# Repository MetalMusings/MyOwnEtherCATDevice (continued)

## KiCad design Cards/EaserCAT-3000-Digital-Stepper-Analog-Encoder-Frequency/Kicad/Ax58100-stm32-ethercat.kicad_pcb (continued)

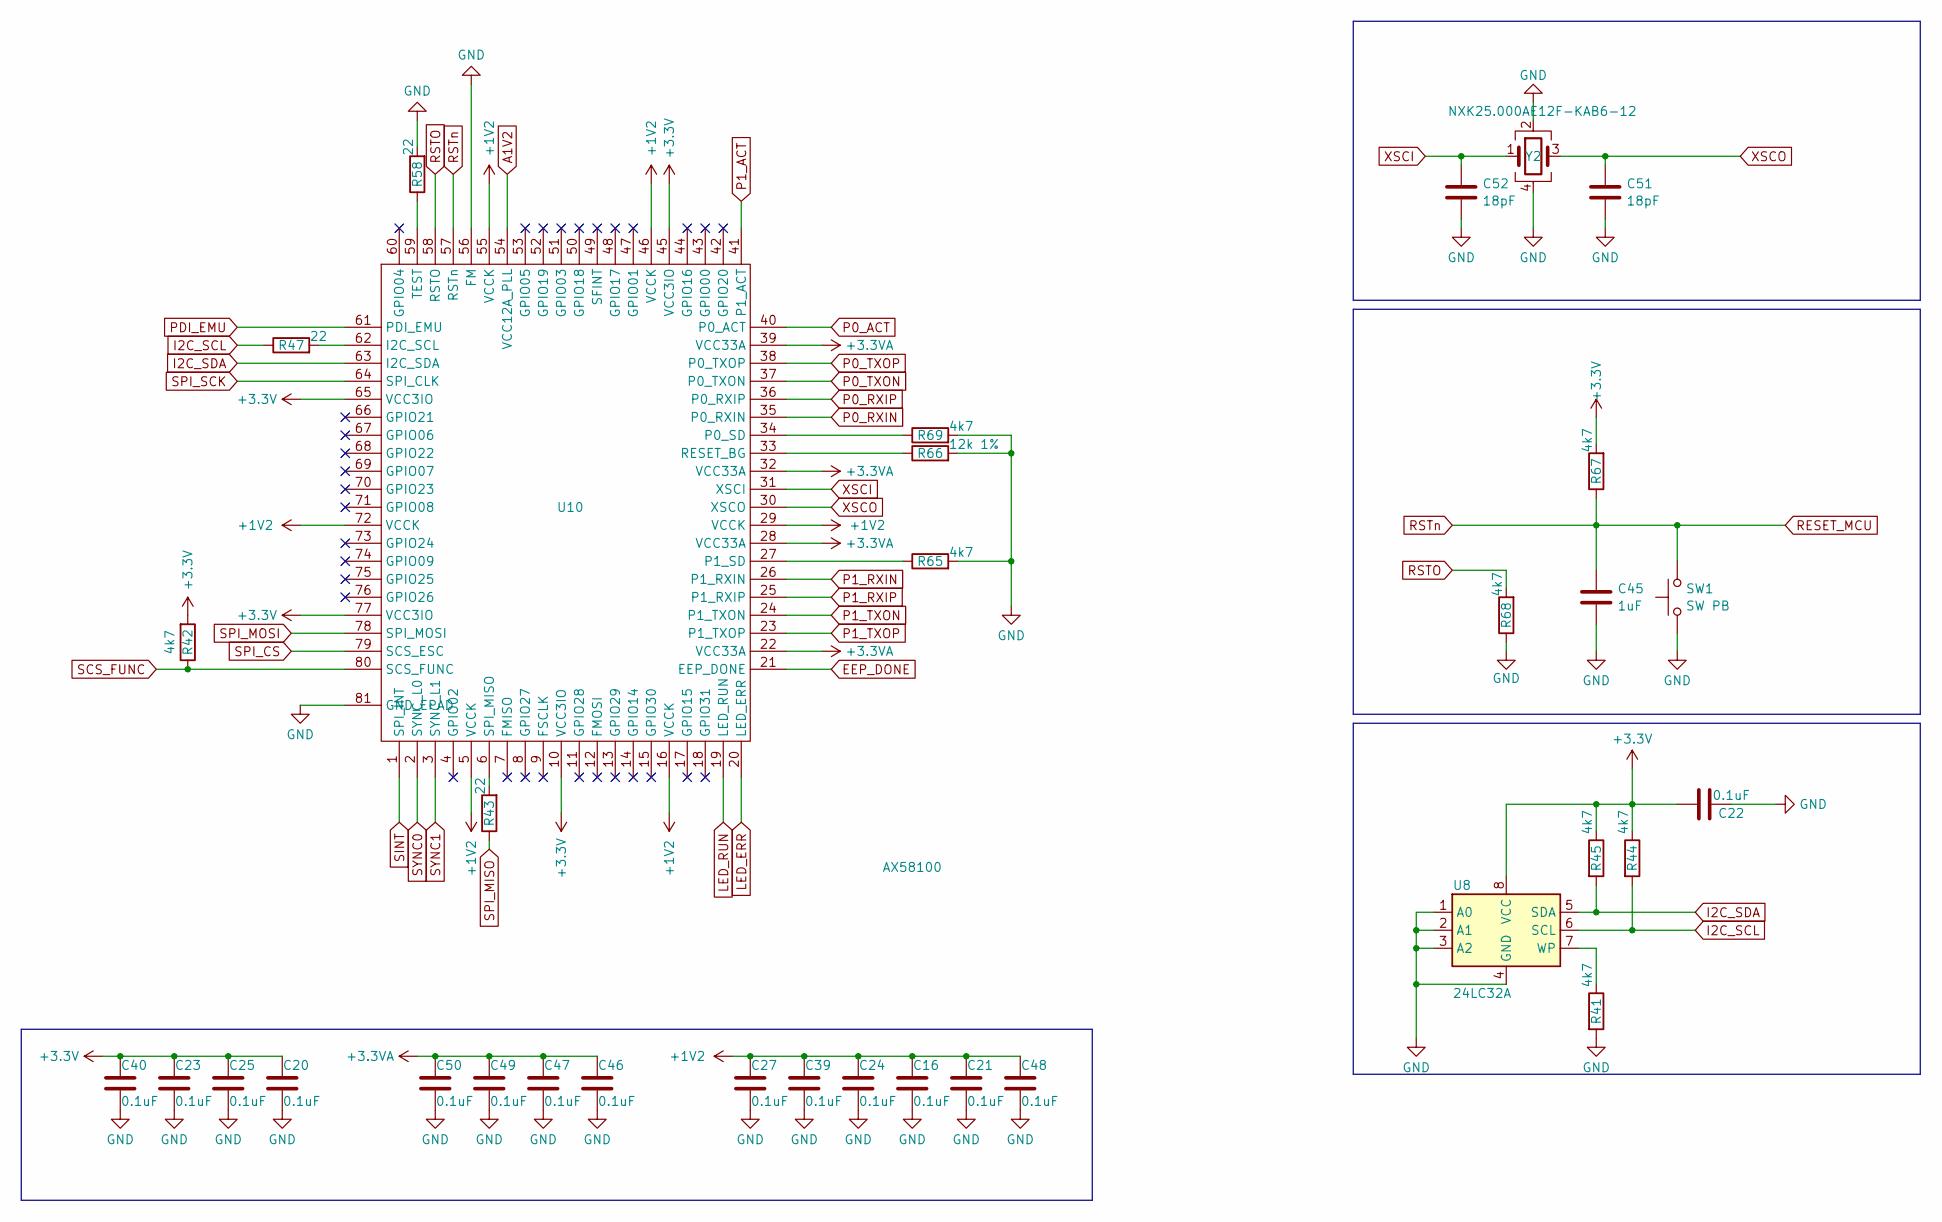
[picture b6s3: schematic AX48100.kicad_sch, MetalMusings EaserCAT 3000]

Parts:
C16, C20, C21, C22, C23, C24, C25, C27, C39, C40, C46, C47, C48, C49, C50: 0.1uF; C_0805_2012Metric
C45: 1uF; C_0805_2012Metric
C51, C52: 18pF; C_0805_2012Metric
R41, R44, R45, R65, R67, R68, R69: 4k7; R_0805_2012Metric
R42: 4k7; R_0603_1608Metric
R43, R47, R58: 22; R_0805_2012Metric
R66: 12k 1%; R_0805_2012Metric
SW1: SW PB; SW_Push_1P1T_XKB_TS-1187A
U8: 24LC32A; SOIC-8_3.9x4.9mm_P1.27mm
U10: AX58100; LQFP-80-1EP_10x10mm_P0.4mm_EP5.3x4.5mm_ThermalVias
Y2: NXK25.000AE12F-KAB6-12; Crystal_SMD_SeikoEpson_TSX3225-4Pin_3.2x2.5mm

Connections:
+1V2: C16.1, C21.1, C24.1, C27.1, C39.1, C48.1, U10.5 (VCCK), U10.16 (VCCK), U10.29 (VCCK), U10.46 (VCCK), U10.55 (VCCK), U10.72 (VCCK); also elsewhere on the board
+3.3V: C20.1, C22.2, C23.1, C25.1, C40.1, R42.2, R44.1, R45.1, R67.2, U8.8 (VCC), U10.10 (VCC3IO), U10.45 (VCC3IO), U10.65 (VCC3IO), U10.77 (VCC3IO); also elsewhere on the board
+3.3VA: C46.1, C47.1, C49.1, C50.1, U10.22 (VCC33A), U10.28 (VCC33A), U10.32 (VCC33A), U10.39 (VCC33A); also elsewhere on the board
A1V2: U10.54 (VCC12A_PLL); also elsewhere on the board
EEP_DONE: U10.21 (EEP_DONE); also elsewhere on the board
GND: C16.2, C20.2, C21.2, C22.1, C23.2, C24.2, C25.2, C27.2, C39.2, C40.2, C45.2, C46.2, C47.2, C48.2, C49.2, C50.2, C51.2, C52.2, R41.2, R58.2, R65.2, R66.2, R68.1, R69.2, SW1.1, U8.1 (A0), U8.2 (A1), U8.3 (A2), U8.4 (GND), U10.56 (FM), U10.81 (GND_EPAD), Y2.2, Y2.4; also elsewhere on the board
I2C_SCL: R44.2, R47.1, U8.6 (SCL)
I2C_SDA: R45.2, U8.5 (SDA), U10.63 (I2C_SDA)
LED_ERR: U10.20 (LED_ERR); also elsewhere on the board
LED_RUN: U10.19 (LED_RUN); also elsewhere on the board
unnamed: R41.1, U8.7 (WP)
unnamed: R47.2, U10.62 (I2C_SCL)
unnamed: R69.1, U10.34 (P0_SD)
unnamed: R65.1, U10.27 (P1_SD)
unnamed: R66.1, U10.33 (RESET_BG)
unnamed: R43.2, U10.6 (SPI_MISO)
unnamed: R58.1, U10.59 (TEST)
P0_ACT: U10.40 (P0_ACT); also elsewhere on the board
P0_RXIN: U10.35 (P0_RXIN); also elsewhere on the board
P0_RXIP: U10.36 (P0_RXIP); also elsewhere on the board
P0_TXON: U10.37 (P0_TXON); also elsewhere on the board
P0_TXOP: U10.38 (P0_TXOP); also elsewhere on the board
P1_ACT: U10.41 (P1_ACT); also elsewhere on the board
P1_RXIN: U10.26 (P1_RXIN); also elsewhere on the board
P1_RXIP: U10.25 (P1_RXIP); also elsewhere on the board
P1_TXON: U10.24 (P1_TXON); also elsewhere on the board
P1_TXOP: U10.23 (P1_TXOP); also elsewhere on the board
PDI_EMU: U10.61 (PDI_EMU); also elsewhere on the board
RESET_MCU: C45.1, R67.1, SW1.2, U10.57 (RSTn); also elsewhere on the board
RSTO: R68.2, U10.58 (RSTO)
SCS_FUNC: R42.1, U10.80 (SCS_FUNC); also elsewhere on the board
SINT: U10.1 (SPI_INT); also elsewhere on the board
SPI_CS: U10.79 (SCS_ESC); also elsewhere on the board
SPI_MISO: R43.1; also elsewhere on the board
SPI_MOSI: U10.78 (SPI_MOSI); also elsewhere on the board
SPI_SCK: U10.64 (SPI_CLK); also elsewhere on the board
SYNC0: U10.2 (SYNC_L0); also elsewhere on the board
SYNC1: U10.3 (SYNC_L1); also elsewhere on the board
XSCI: C52.1, U10.31 (XSCI), Y2.1
XSCO: C51.1, U10.30 (XSCO), Y2.3

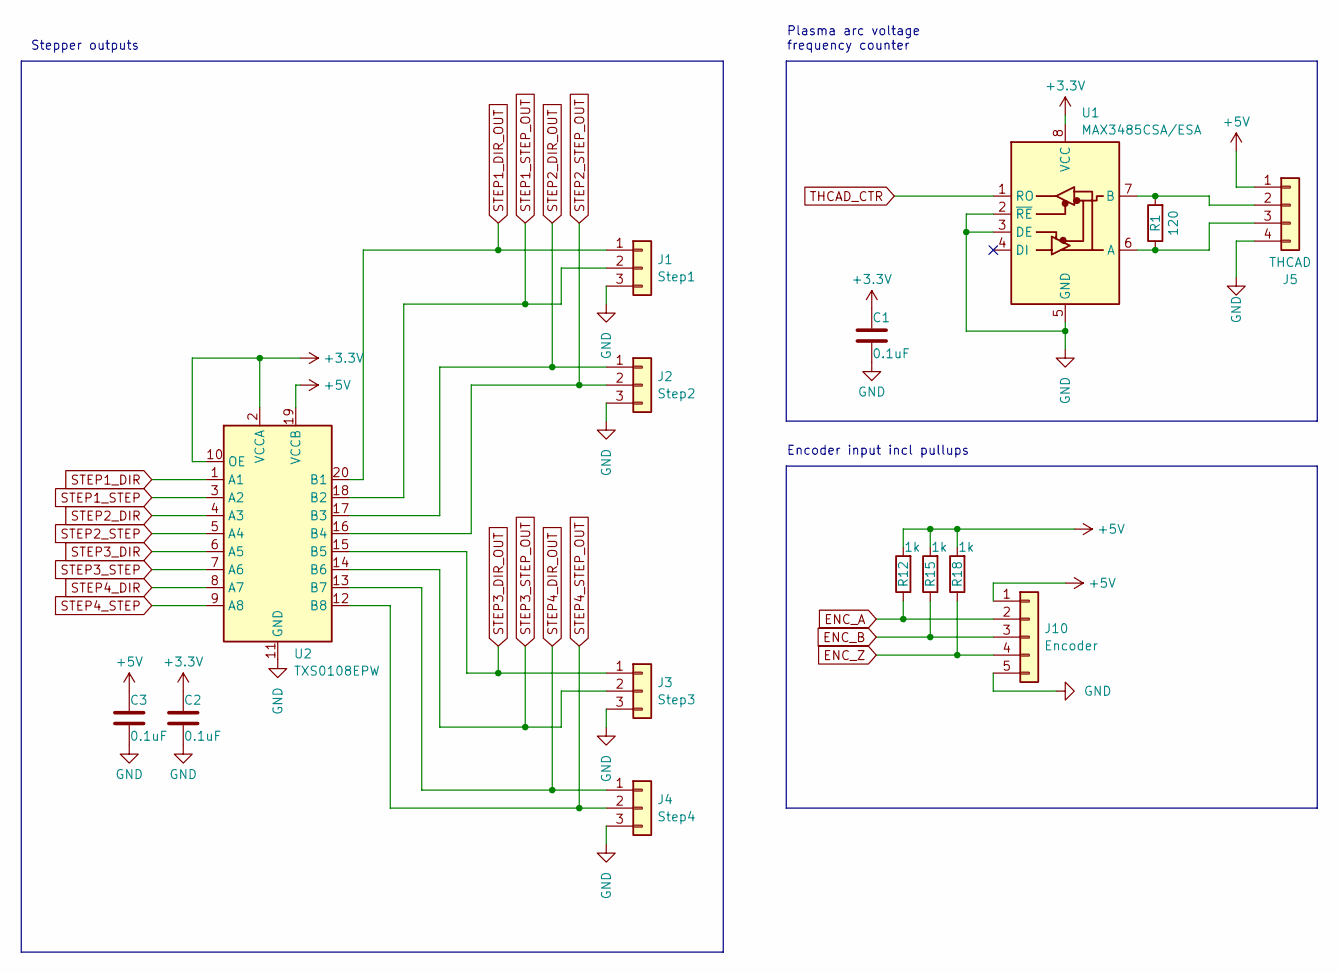
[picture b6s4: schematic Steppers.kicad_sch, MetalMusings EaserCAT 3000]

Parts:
C1, C2, C3: 0.1uF; C_0805_2012Metric
J1: Step1; PhoenixContact_MCV_1,5_3-G-3.5_1x03_P3.50mm_Vertical
J2: Step2; PhoenixContact_MCV_1,5_3-G-3.5_1x03_P3.50mm_Vertical
J3: Step3; PhoenixContact_MCV_1,5_3-G-3.5_1x03_P3.50mm_Vertical
J4: Step4; PhoenixContact_MCV_1,5_3-G-3.5_1x03_P3.50mm_Vertical
J5: THCAD; PhoenixContact_MCV_1,5_4-G-3.5_1x04_P3.50mm_Vertical
J10: Encoder; PhoenixContact_MCV_1,5_5-G-3.5_1x05_P3.50mm_Vertical
R1: 120; R_0805_2012Metric
R12, R15, R18: 1k; R_0805_2012Metric
U1: MAX3485CSA/ESA; SO-8_3.9x4.9mm_P1.27mm
U2: TXS0108EPW; TSSOP-20_4.4x6.5mm_P0.65mm

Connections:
+3.3V: C1.1, C2.1, U1.8 (VCC), U2.2 (VCCA), U2.10 (OE); also elsewhere on the board
+5V: C3.1, J5.1, J10.1, R12.2, R15.2, R18.2, U2.19 (VCCB); also elsewhere on the board
ENC_A: J10.2, R12.1; also elsewhere on the board
ENC_B: J10.3, R15.1; also elsewhere on the board
ENC_Z: J10.4, R18.1; also elsewhere on the board
GND: C1.2, C2.2, C3.2, J1.3, J2.3, J3.3, J4.3, J5.4, J10.5, U1.2 (~RE), U1.3 (DE), U1.5 (GND), U2.11 (GND); also elsewhere on the board
unnamed: J5.2, R1.2, U1.7 (B)
unnamed: J5.3, R1.1, U1.6 (A)
STEP1_DIR: U2.1 (A1); also elsewhere on the board
STEP1_DIR_OUT: J1.1, U2.20 (B1)
STEP1_STEP: U2.3 (A2); also elsewhere on the board
STEP1_STEP_OUT: J1.2, U2.18 (B2)
STEP2_DIR: U2.4 (A3); also elsewhere on the board
STEP2_DIR_OUT: J2.1, U2.17 (B3)
STEP2_STEP: U2.5 (A4); also elsewhere on the board
STEP2_STEP_OUT: J2.2, U2.16 (B4)
STEP3_DIR: U2.6 (A5); also elsewhere on the board
STEP3_DIR_OUT: J3.1, U2.15 (B5)
STEP3_STEP: U2.7 (A6); also elsewhere on the board
STEP3_STEP_OUT: J3.2, U2.14 (B6)
STEP4_DIR: U2.8 (A7); also elsewhere on the board
STEP4_DIR_OUT: J4.1, U2.13 (B7)
STEP4_STEP: U2.9 (A8); also elsewhere on the board
STEP4_STEP_OUT: J4.2, U2.12 (B8)
THCAD_CTR: U1.1 (RO); also elsewhere on the board

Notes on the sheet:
Encoder input incl pullups
Plasma arc voltage frequency counter
Stepper outputs

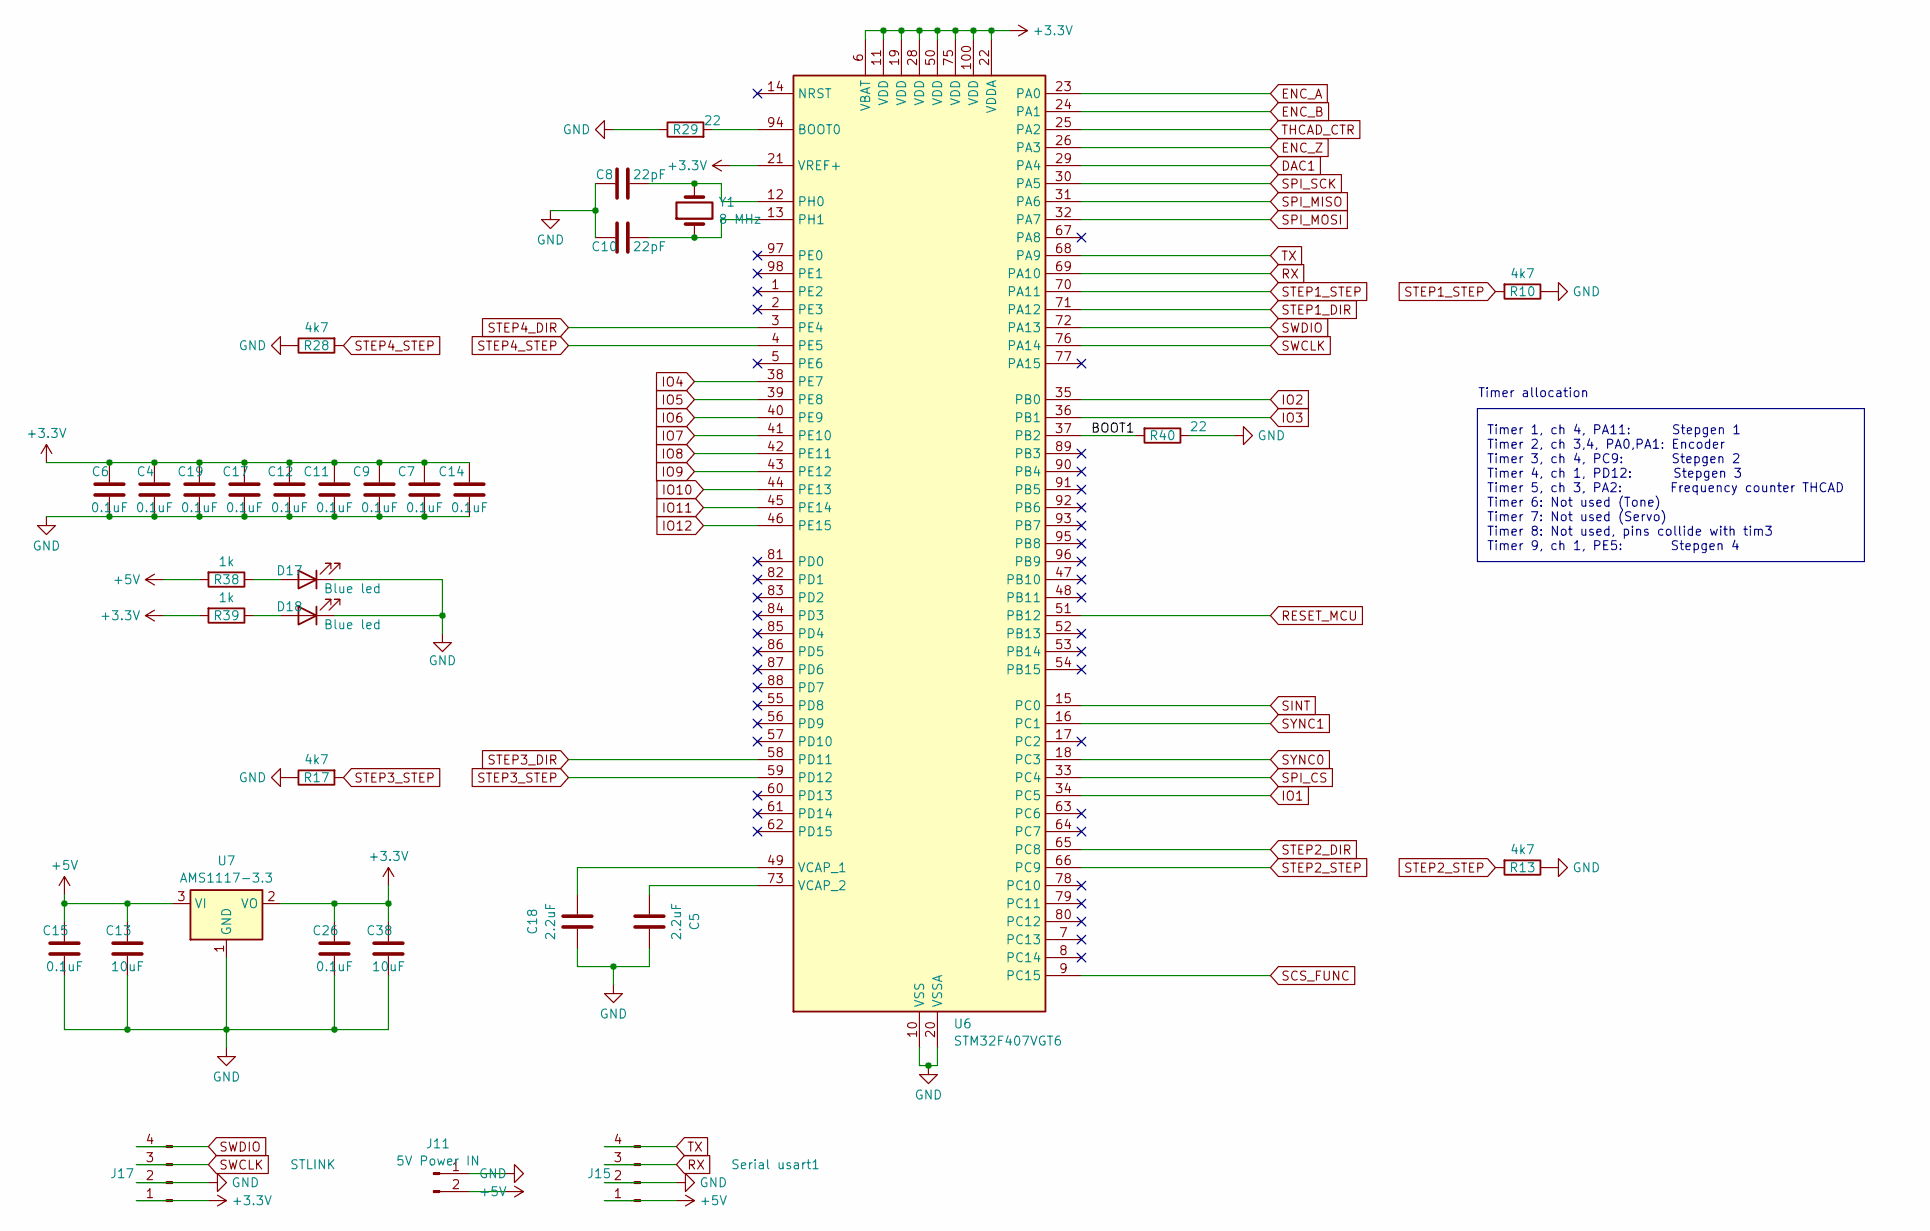
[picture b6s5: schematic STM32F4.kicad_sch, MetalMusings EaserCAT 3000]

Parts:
C4, C6, C7, C9, C11, C12, C14, C15, C17, C19, C26: 0.1uF; C_0805_2012Metric
C5, C18: 2.2uF; C_0805_2012Metric
C8, C10: 22pF; C_0805_2012Metric
C13, C38: 10uF; C_0805_2012Metric
D17, D18: Blue led; LED_0603_1608Metric
J11: 5V Power IN; PhoenixContact_MCV_1,5_2-G-3.5_1x02_P3.50mm_Vertical
J15: Serial usart1; JST_XH_B4B-XH-A_1x04_P2.50mm_Vertical
J17: STLINK; JST_XH_B4B-XH-A_1x04_P2.50mm_Vertical
R10, R13, R17, R28: 4k7; R_0805_2012Metric
R29, R40: 22; R_0805_2012Metric
R38, R39: 1k; R_0805_2012Metric
U6: STM32F407VGT6; LQFP-100_14x14mm_P0.5mm
U7: AMS1117-3.3; SOT-223-3_TabPin2
Y1: 8 MHz; Crystal_HC49-4H_Vertical

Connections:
+3.3V: C4.1, C6.1, C7.1, C9.1, C11.1, C12.1, C14.1, C17.1, C19.1, C26.1, C38.1, J17.1, R39.2, U6.6 (VBAT), U6.11 (VDD), U6.19 (VDD), U6.21 (VREF+), U6.22 (VDDA), U6.28 (VDD), U6.50 (VDD), U6.75 (VDD), U6.100 (VDD), U7.2 (VO); also elsewhere on the board
+5V: C13.1, C15.1, J11.2, J15.1, R38.2, U7.3 (VI); also elsewhere on the board
/STM32F4/BOOT1: R40.2, U6.37 (PB2)
DAC1: U6.29 (PA4); also elsewhere on the board
ENC_A: U6.23 (PA0); also elsewhere on the board
ENC_B: U6.24 (PA1); also elsewhere on the board
ENC_Z: U6.26 (PA3); also elsewhere on the board
GND: C4.2, C5.1, C6.2, C7.2, C8.1, C9.2, C10.1, C11.2, C12.2, C13.2, C14.2, C15.2, C17.2, C18.1, C19.2, C26.2, C38.2, D17.1 (K), D18.1 (K), J11.1, J15.2, J17.2, R10.1, R13.1, R17.1, R28.1, R29.1, R40.1, U6.10 (VSS), U6.20 (VSSA), U6.27 (VSS), U6.74 (VSS), U6.99 (VSS), U7.1 (GND); also elsewhere on the board
IO1: U6.34 (PC5); also elsewhere on the board
IO2: U6.35 (PB0); also elsewhere on the board
IO3: U6.36 (PB1); also elsewhere on the board
IO4: U6.38 (PE7); also elsewhere on the board
IO5: U6.39 (PE8); also elsewhere on the board
IO6: U6.40 (PE9); also elsewhere on the board
IO7: U6.41 (PE10); also elsewhere on the board
IO8: U6.42 (PE11); also elsewhere on the board
IO9: U6.43 (PE12); also elsewhere on the board
IO10: U6.44 (PE13); also elsewhere on the board
IO11: U6.45 (PE14); also elsewhere on the board
IO12: U6.46 (PE15); also elsewhere on the board
unnamed: D17.2 (A), R38.1
unnamed: D18.2 (A), R39.1
unnamed: R29.2, U6.94 (BOOT0)
unnamed: C8.2, U6.12 (PH0), Y1.2
unnamed: C10.2, U6.13 (PH1), Y1.1
unnamed: C18.2, U6.49 (VCAP_1)
unnamed: C5.2, U6.73 (VCAP_2)
RESET_MCU: U6.51 (PB12); also elsewhere on the board
RX: J15.3, U6.69 (PA10)
SCS_FUNC: U6.9 (PC15); also elsewhere on the board
SINT: U6.15 (PC0); also elsewhere on the board
SPI_CS: U6.33 (PC4); also elsewhere on the board
SPI_MISO: U6.31 (PA6); also elsewhere on the board
SPI_MOSI: U6.32 (PA7); also elsewhere on the board
SPI_SCK: U6.30 (PA5); also elsewhere on the board
STEP1_DIR: U6.71 (PA12); also elsewhere on the board
STEP1_STEP: R10.2, U6.70 (PA11); also elsewhere on the board
STEP2_DIR: U6.65 (PC8); also elsewhere on the board
STEP2_STEP: R13.2, U6.66 (PC9); also elsewhere on the board
STEP3_DIR: U6.58 (PD11); also elsewhere on the board
STEP3_STEP: R17.2, U6.59 (PD12); also elsewhere on the board
STEP4_DIR: U6.3 (PE4); also elsewhere on the board
STEP4_STEP: R28.2, U6.4 (PE5); also elsewhere on the board
SWCLK: J17.3, U6.76 (PA14)
SWDIO: J17.4, U6.72 (PA13)
SYNC0: U6.18 (PC3); also elsewhere on the board
SYNC1: U6.16 (PC1); also elsewhere on the board
THCAD_CTR: U6.25 (PA2); also elsewhere on the board
TX: J15.4, U6.68 (PA9)

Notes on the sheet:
Timer allocation
Timer 1, ch 4, PA11: Stepgen 1 Timer 2, ch 3,4, PA0,PA1: Encoder Timer 3, ch 4, PC9: Stepgen 2 Timer 4, ch 1, PD12: Stepgen 3 Timer 5, ch 3, PA2: Frequency counter THCAD Timer 6: Not used (Tone) Timer 7: Not used (Servo) Timer 8: Not used, pins collide with tim3 Timer 9, ch 1, PE5: Stepgen 4

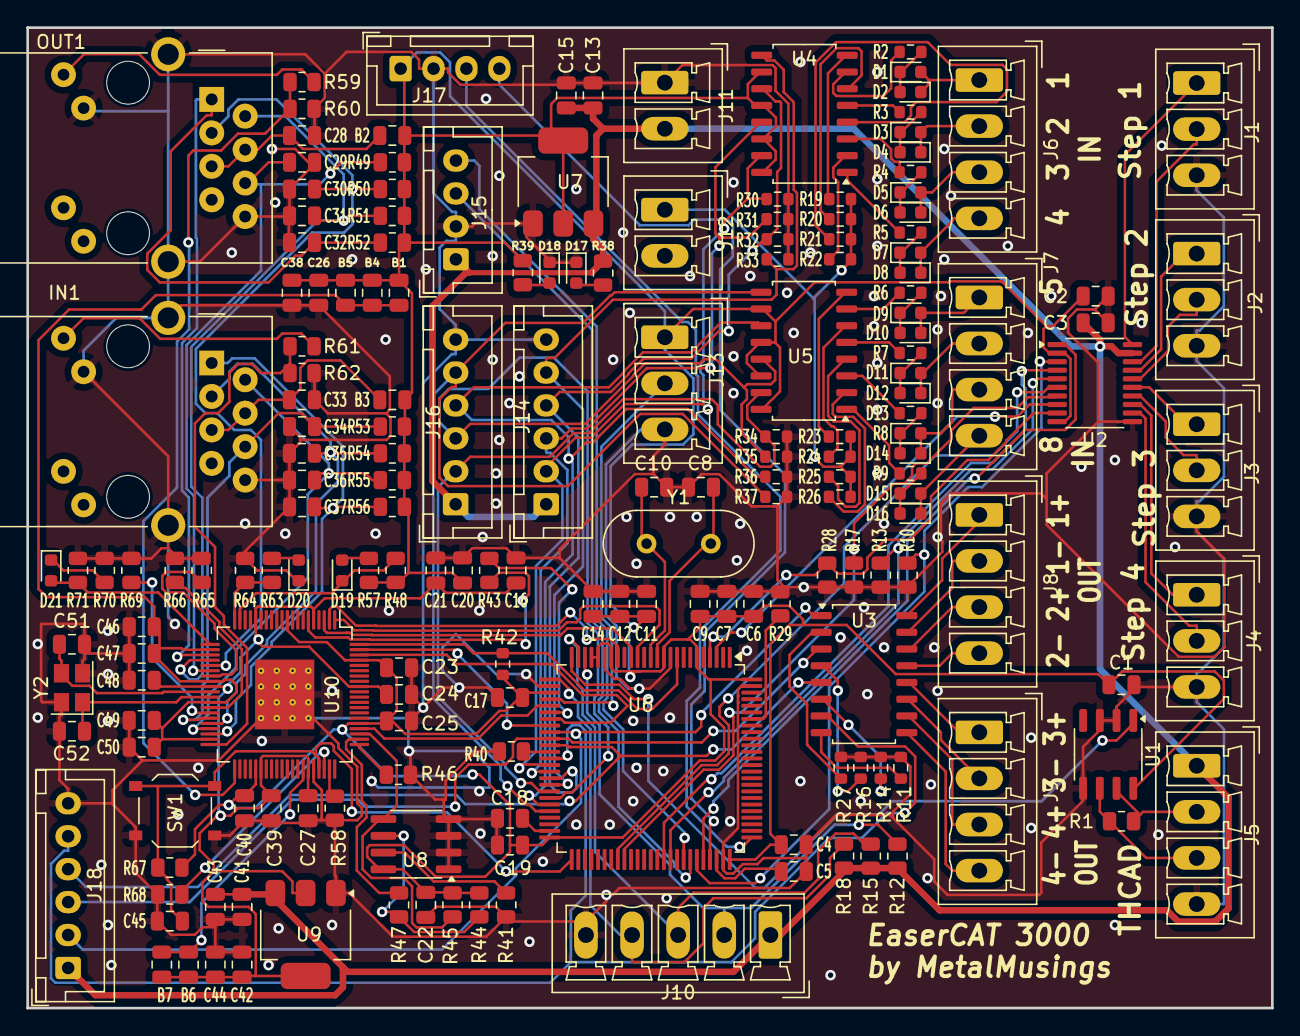
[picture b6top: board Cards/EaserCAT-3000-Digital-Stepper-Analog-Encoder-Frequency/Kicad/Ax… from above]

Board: 2 copper layers, 94.5 x 74.4 mm, 184 parts (0 on the bottom side), 140 nets.

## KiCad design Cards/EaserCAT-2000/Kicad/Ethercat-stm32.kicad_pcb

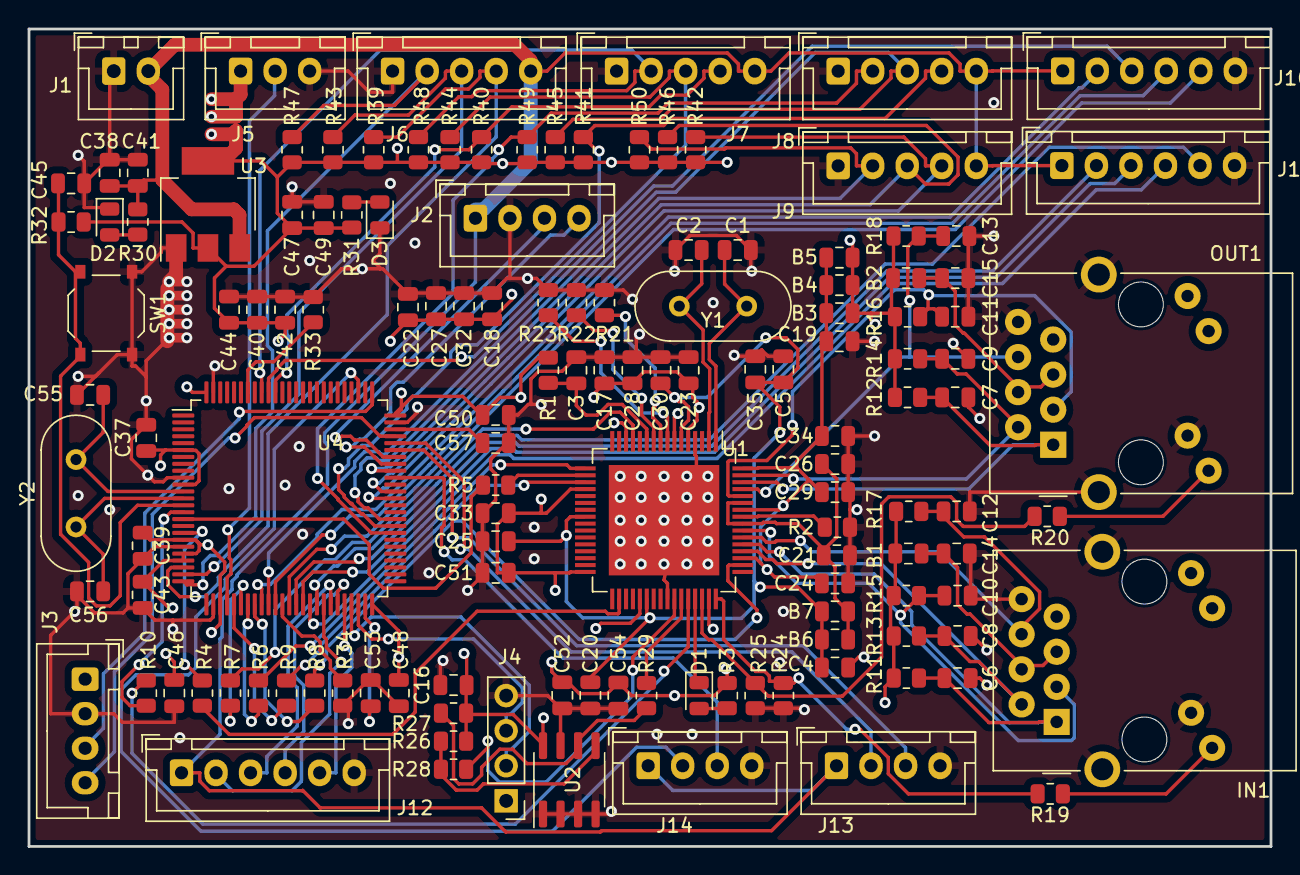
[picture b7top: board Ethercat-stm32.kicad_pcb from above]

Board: 4 copper layers, 89.9 x 59.2 mm, 134 parts (0 on the bottom side), 91 nets.

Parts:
B1, B2: BLM18EG221S; C_0805_2012Metric
B3, B4, B5, B6, B7: BLM18EG221SN1D; C_0805_2012Metric
C1, C2: 20pF; C_0805_2012Metric
C3, C14, C15, C16, C17, C18, C19, C20, C21, C22, C23, C24, C25, C26, C27, C28, C29, C30, C32, C33, C34, C35, C37, C38, C39, C40, C42, C43, C44, C45, C46, C47, C48, C50, C51, C52, C54: 0.1uF; C_0805_2012Metric
C4: 470pF; C_0805_2012Metric
C5: 1uF; C_0805_2012Metric
C6, C7, C8, C9, C10, C11, C12, C13: 10pF; C_0805_2012Metric
C41, C49: 10uF; C_0805_2012Metric
C53, C57: 2.2uF; C_0805_2012Metric
C55, C56: 22pF; C_0805_2012Metric
D1: Green led; LED_0805_2012Metric
D2, D3: Blue led; LED_0805_2012Metric
IN1: J0011D01BNL; PulseJack JB0011D01BNL
J1: Conn_01x02_Pin; JST_XH_B2B-XH-A_1x02_P2.50mm_Vertical
J2: Serial usart1; JST_XH_B4B-XH-A_1x04_P2.50mm_Vertical
J3: STLINK; JST_XH_B4B-XH-A_1x04_P2.50mm_Vertical
J4: I2C bus2; PinHeader_1x04_P2.54mm_Vertical
J5: DAC1; JST_XH_B3B-XH-A_1x03_P2.50mm_Vertical
J6: Encoder 1; JST_XH_B5B-XH-A_1x05_P2.50mm_Vertical
J7: Encoder 2; JST_XH_B5B-XH-A_1x05_P2.50mm_Vertical
J8: Encoder 3; JST_XH_B5B-XH-A_1x05_P2.50mm_Vertical
J9: Encoder 4; JST_XH_B5B-XH-A_1x05_P2.50mm_Vertical
J10, J11, J12: Conn_01x06_Pin; JST_XH_B6B-XH-A_1x06_P2.50mm_Vertical
J13: Stepper 1; JST_XH_B4B-XH-A_1x04_P2.50mm_Vertical
J14: Stepper 2; JST_XH_B4B-XH-A_1x04_P2.50mm_Vertical
OUT1: J0011D01BNL; PulseJack JB0011D01BNL
R1, R21, R22, R23, R24, R25: 10k; R_0805_2012Metric
R2: 12.1k; R_0805_2012Metric
R3, R19, R20, R30, R31, R32, R39, R40, R41, R42, R43, R44, R45, R46, R47, R48, R49, R50: 1k; R_0805_2012Metric
R4, R5, R6, R7, R8, R9, R10, R28, R29, R33, R34: 22; R_0805_2012Metric
R11, R12, R13, R14, R15, R16, R17, R18: 49.9; R_0805_2012Metric
R26, R27: 2k; R_0805_2012Metric
SW1: SW_Push; SW_Push_1P1T_XKB_TS-1187A
U1: LAN9252_PT; TQFP-64-1EP_10x10mm_P0.5mm_EP8x8mm
U2: AT24CS32-SSHM; SOIC-8_3.9x4.9mm_P1.27mm
U3: AMS1117-3.3; SOT-223-3_TabPin2
U4: STM32F407VGT6; LQFP-100_14x14mm_P0.5mm
Y1: 25MHz; Crystal_HC49-U_Vertical
Y2: 8 MHz; Crystal_HC49-U_Vertical

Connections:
+1V2: B6.1, B7.1, C4.1, C5.1, C20.1, C25.1, C30.1, C35.1, U1.6 (VDDCR), U1.24 (VDDCR), U1.38 (VDDCR)
+3.3V: B1.1, B2.1, B3.1, B4.1, B5.1, C16.2, C17.1, C18.1, C22.1, C23.1, C27.1, C28.1, C32.1, C33.1, C37.1, C39.1, C40.1, C42.1, C43.1, C44.1, C46.1, C47.1, C48.1, C49.1, C50.1, C51.1, C52.1, C54.1, J3.1, J4.1, J5.1, R1.1, R3.1, R11.2, R12.2, R13.2, R14.2, R15.2, R16.2, R17.2, R18.2, R26.1, R27.1, R31.2, R32.2, R39.2, R40.2, R41.2, R42.2, R43.2, R44.2, R45.2, R46.2, R47.2, R48.2, R49.2, R50.2, U1.5 (VDD33), U1.7 (REG_EN), U1.14 (VDDIO), U1.20 (VDDIO), U1.32 (VDDIO), U1.37 (VDDIO), U1.47 (VDDIO), U2.8 (VCC), U3.2 (VO), U4.6 (VBAT), U4.11 (VDD), U4.19 (VDD), U4.21 (VREF+), U4.22 (VDDA), U4.28 (VDD), U4.50 (VDD), U4.75 (VDD), U4.100 (VDD)
+3.3VA: B3.2, B4.2, B5.2, C19.1, C24.1, C29.1, C34.1, U1.51 (VDD33TXRX1), U1.58 (VDD33BIAS), U1.64 (VDD33TXRX2)
+5V: C38.1, C41.1, J1.2, J2.1, J6.5, J7.5, J8.5, J9.5, J10.1, J11.1, J12.1, J13.1, J14.1, R30.2, U3.3 (VI)
/STM32F4/BOOT1: R34.2, U4.37 (PB2)
DAC1: J5.2, U4.29 (PA4)
ENC1_A: J6.4, R39.1, U4.23 (PA0)
ENC1_B: J6.3, R43.1, U4.24 (PA1)
ENC1_Z: J6.2, R47.1, U4.25 (PA2)
ENC2_A: J7.4, R40.1, U4.90 (PB4)
ENC2_B: J7.3, R44.1, U4.91 (PB5)
ENC2_Z: J7.2, R48.1, U4.92 (PB6)
ENC3_A: J8.4, R41.1, U4.59 (PD12)
ENC3_B: J8.3, R45.1, U4.60 (PD13)
ENC3_Z: J8.2, R49.1, U4.58 (PD11)
ENC4_A: J9.4, R42.1, U4.63 (PC6)
ENC4_B: J9.3, R46.1, U4.64 (PC7)
ENC4_Z: J9.2, R50.1, U4.67 (PA8)
FXLOSA: R21.1, U1.9 (FXSDA/FXLOSA/~FXSDENA)
FXLOSB: R22.1, U1.10 (FXSDB/FXLOSB/~FXSDENB)
FXLOSEN: R23.1, U1.8 (~FXLOSEN)
GND: C1.1, C2.1, C3.1, C4.2, C5.2, C6.1, C7.1, C8.1, C9.1, C10.1, C11.1, C12.1, C13.1, C14.1, C15.1, C16.1, C17.2, C18.2, C19.2, C20.2, C21.2, C22.2, C23.2, C24.2, C25.2, C26.2, C27.2, C28.2, C29.2, C30.2, C32.2, C33.2, C34.2, C35.2, C37.2, C38.2, C39.2, C40.2, C41.2, C42.2, C43.2, C44.2, C45.1, C46.2, C47.2, C48.2, C49.2, C50.2, C51.2, C52.2, C53.1, C54.2, C55.1, C56.1, C57.1, D2.1 (K), D3.1 (K), IN1.8 (CHS_GND), IN1.10, IN1.SH (CHS_GND), J1.1, J2.2, J3.2, J4.4, J5.3, J6.1, J7.1, J8.1, J9.1, J10.6, J11.6, J12.6, J13.4, J14.4, OUT1.8 (CHS_GND), OUT1.10, OUT1.SH (CHS_GND), R2.1, R21.2, R22.2, R23.2, R24.2, R25.2, R33.1, R34.1, SW1.1, U1.4 (OSCVSS), U1.41 (TESTMODE), U1.65 (VSS), U2.1 (A0), U2.2 (A1), U2.3 (A2), U2.4 (GND), U2.7 (WP), U3.1 (GND), U4.10 (VSS), U4.20 (VSSA), U4.27 (VSS), U4.74 (VSS), U4.99 (VSS)
GPIO0: R19.1, R24.1, U1.48 (LINKACTLED0/TDO/~CHIP_MODE0)
GPIO1: R20.1, R25.1, U1.46 (LINKACTLED1/TDI/~CHIP_MODE1)
I2C2_SCL: J4.2, U4.47 (PB10)
I2C2_SDA: J4.3, U4.48 (PB11)
I2C_SCL: R29.1, U1.43 (EESCL/TCK)
I2C_SDA: R28.1, U1.42 (EESDA/TMS)
IO1: J10.2, U4.34 (PC5)
IO2: J10.3, U4.35 (PB0)
IO3: J10.4, U4.36 (PB1)
IO4: J10.5, U4.38 (PE7)
IO5: J11.2, U4.39 (PE8)
IO6: J11.3, U4.40 (PE9)
IO7: J11.4, U4.41 (PE10)
IO8: J11.5, U4.42 (PE11)
IO9: J12.2, U4.43 (PE12)
IO10: J12.3, U4.44 (PE13)
IO11: J12.4, U4.45 (PE14)
IO12: J12.5, U4.46 (PE15)
IRQ: R10.1, U4.15 (PC0)
NRST: C45.2, R32.1, SW1.2, U4.14 (NRST)
unnamed: D1.2 (A), R3.2
unnamed: D1.1 (K), U1.45 (RUNLED/~E2PSIZE)
unnamed: D2.2 (A), R30.1
unnamed: D3.2 (A), R31.1
unnamed: IN1.9, R19.2
unnamed: B1.2, C14.2, IN1.4 (TCT), IN1.5 (RCT)
unnamed: OUT1.9, R20.2
unnamed: B2.2, C15.2, OUT1.4 (TCT), OUT1.5 (RCT)
unnamed: R6.2, U1.17 (D0/AD0/WD_STATE/SI/SIO0)
unnamed: R7.2, U1.13 (D1/AD1/EOF/SO/SIO1)
unnamed: R8.2, U1.50 (D5/AD5/OUTVALID/SCS#)
unnamed: R9.2, U1.19 (D9/AD9/LATCH_IN/SCK)
unnamed: R10.2, U1.44 (IRQ)
unnamed: C1.2, U1.1 (OSCI), Y1.2
unnamed: C2.2, U1.2 (OSCO), Y1.1
unnamed: R2.2, U1.57 (RBIAS)
unnamed: R4.1, U1.34 (SYNC0/LATCH0)
unnamed: R5.1, U1.18 (SYNC1/LATCH1)
unnamed: C3.2, R1.2, U1.11 (~RST)
unnamed: R27.2, R29.2, U2.6 (SCL)
unnamed: R26.2, R28.2, U2.5 (SDA)
unnamed: R33.2, U4.94 (BOOT0)
unnamed: C55.2, U4.12 (PH0), Y2.2
unnamed: C56.2, U4.13 (PH1), Y2.1
unnamed: C53.2, U4.49 (VCAP_1)
unnamed: C57.2, U4.73 (VCAP_2)
RX: J2.3, U4.69 (PA10)
RXNA: C12.2, IN1.6 (RD-), R17.1, U1.54 (RXNA)
RXNB: C13.2, OUT1.6 (RD-), R18.1, U1.61 (RXNB)
RXPA: C10.2, IN1.3 (RD+), R15.1, U1.55 (RXPA)
RXPB: C11.2, OUT1.3 (RD+), R16.1, U1.60 (RXPB)
SPI_CS: R8.1, U4.33 (PC4)
SPI_MISO: R7.1, U4.31 (PA6)
SPI_MOSI: R6.1, U4.32 (PA7)
SPI_SCK: R9.1, U4.30 (PA5)
STEP1_DIR: J13.2, U4.71 (PA12)
STEP1_STEP: J13.3, U4.70 (PA11)
STEP2_DIR: J14.2, U4.78 (PC10)
STEP2_STEP: J14.3, U4.66 (PC9)
SWCLK: J3.3, U4.76 (PA14)
SWDIO: J3.4, U4.72 (PA13)
SYNC0: R4.2, U4.18 (PC3)
SYNC1: R5.2, U4.16 (PC1)
TX: J2.4, U4.68 (PA9)
TXNA: C8.2, IN1.2 (TD-), R13.1, U1.52 (TXNA)
TXNB: C9.2, OUT1.2 (TD-), R14.1, U1.63 (TXNB)
TXPA: C6.2, IN1.1 (TD+), R11.1, U1.53 (TXPA)
TXPB: C7.2, OUT1.1 (TD+), R12.1, U1.62 (TXPB)
VDD12TX1: B6.2, B7.2, C21.1, C26.1, U1.56 (VDD12TX1), U1.59 (VDD12TX2)

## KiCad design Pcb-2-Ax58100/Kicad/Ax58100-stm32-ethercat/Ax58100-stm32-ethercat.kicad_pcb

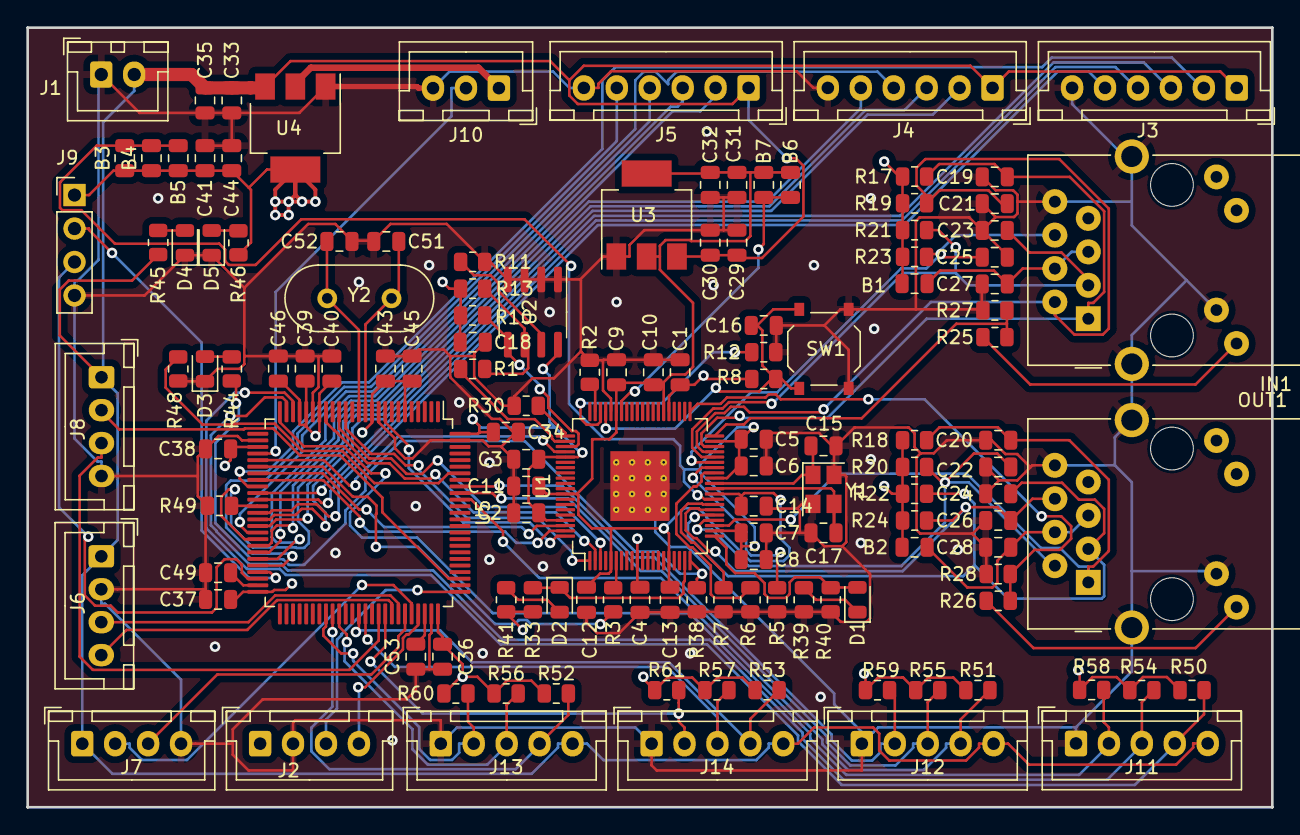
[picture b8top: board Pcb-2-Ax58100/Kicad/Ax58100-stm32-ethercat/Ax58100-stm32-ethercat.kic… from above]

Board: 4 copper layers, 94.5 x 59.2 mm, 131 parts (0 on the bottom side), 91 nets.

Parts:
B1, B2: BLM18EG221S; C_0805_2012Metric
B3, B4, B5, B6, B7: BLM18EG221SN1D; C_0805_2012Metric
C1, C2, C3, C4, C5, C6, C7, C8, C9, C10, C11, C12, C13, C14, C18, C27, C28, C29, C31, C33, C34, C36, C37, C38, C39, C40, C41, C43, C45, C46: 0.1uF; C_0805_2012Metric
C15, C17: 18pF; C_0805_2012Metric
C16: 1uF; C_0805_2012Metric
C19, C20, C21, C22, C23, C24, C25, C26: 10pF; C_0805_2012Metric
C30, C32, C35, C44: 10uF; C_0805_2012Metric
C49, C53: 2.2uF; C_0805_2012Metric
C51, C52: 22pF; C_0805_2012Metric
D1, D2: Green led; LED_0805_2012Metric
D3: Red led; LED_0805_2012Metric
D4, D5: Blue led; LED_0805_2012Metric
IN1: J0011D01BNL; PulseJack JB0011D01BNL
J1: Conn_01x02_Pin; JST_XH_B2B-XH-A_1x02_P2.50mm_Vertical
J2: STLINK; JST_XH_B4B-XH-A_1x04_P2.50mm_Vertical
J3, J4, J5: Conn_01x06_Pin; JST_XH_B6B-XH-A_1x06_P2.50mm_Vertical
J6: Serial usart1; JST_XH_B4B-XH-A_1x04_P2.50mm_Vertical
J7: Stepper 1; JST_XH_B4B-XH-A_1x04_P2.50mm_Vertical
J8: Stepper 2; JST_XH_B4B-XH-A_1x04_P2.50mm_Vertical
J9: I2C bus2; PinHeader_1x04_P2.54mm_Vertical
J10: DAC1; JST_XH_B3B-XH-A_1x03_P2.50mm_Vertical
J11: Encoder 1; JST_XH_B5B-XH-A_1x05_P2.50mm_Vertical
J12: Encoder 2; JST_XH_B5B-XH-A_1x05_P2.50mm_Vertical
J13: Encoder 3; JST_XH_B5B-XH-A_1x05_P2.50mm_Vertical
J14: Encoder 4; JST_XH_B5B-XH-A_1x05_P2.50mm_Vertical
OUT1: J0011D01BNL; PulseJack JB0011D01BNL
R1, R2, R3, R48, R49: 22; R_0805_2012Metric
R5, R7, R8, R10, R11, R12, R13, R30, R33, R38, R40: 4.7k; R_0805_2012Metric
R6: 12k 1%; R_0805_2012Metric
R17, R18, R19, R20, R21, R22, R23, R24: 49.9; R_0805_2012Metric
R25, R26, R27, R28, R39, R41, R44: 510; R_0805_2012Metric
R45, R46, R50, R51, R52, R53, R54, R55, R56, R57, R58, R59, R60, R61: 1k; R_0805_2012Metric
SW1: SW PB; SW_Push_1P1T_XKB_TS-1187A
U1: AX58100; LQFP-80-1EP_10x10mm_P0.4mm_EP5.3x4.5mm_ThermalVias
U2: 24LC32A; SOIC-8_3.9x4.9mm_P1.27mm
U3: AMS1117-1.2; SOT-223-3_TabPin2
U4: AMS1117-3.3; SOT-223-3_TabPin2
U5: STM32F407VGT6; LQFP-100_14x14mm_P0.5mm
Y1: NXK25.000AE12F-KAB6-12; Crystal_SMD_SeikoEpson_TSX3225-4Pin_3.2x2.5mm
Y2: 8 MHz; Crystal_HC49-U_Vertical

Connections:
+1V2: B6.1, B7.1, C9.1, C10.1, C11.1, C12.1, C13.1, C14.1, C31.1, C32.1, U1.5 (VCCK), U1.16 (VCCK), U1.29 (VCCK), U1.46 (VCCK), U1.55 (VCCK), U1.72 (VCCK), U3.2 (VO)
+3.3V: B1.1, B2.1, B3.1, B4.1, B5.1, C1.1, C2.1, C3.1, C4.1, C18.2, C34.1, C36.1, C37.1, C38.1, C39.1, C40.1, C41.1, C43.1, C44.1, C45.1, C46.1, J2.1, J9.1, J10.1, R8.2, R10.1, R13.1, R17.2, R18.2, R19.2, R20.2, R21.2, R22.2, R23.2, R24.2, R33.1, R41.1, R46.2, R50.2, R51.2, R52.2, R53.2, R54.2, R55.2, R56.2, R57.2, R58.2, R59.2, R60.2, R61.2, U1.10 (VCC3IO), U1.45 (VCC3IO), U1.65 (VCC3IO), U1.77 (VCC3IO), U2.8 (VCC), U4.2 (VO), U5.6 (VBAT), U5.11 (VDD), U5.19 (VDD), U5.21 (VREF+), U5.22 (VDDA), U5.28 (VDD), U5.50 (VDD), U5.75 (VDD), U5.100 (VDD)
+3.3VA: B3.2, B4.2, B5.2, C5.1, C6.1, C7.1, C8.1, U1.22 (VCC33A), U1.28 (VCC33A), U1.32 (VCC33A), U1.39 (VCC33A)
+5V: C29.1, C30.1, C33.1, C35.1, J1.2, J3.1, J4.1, J5.1, J6.1, J7.1, J8.1, J11.5, J12.5, J13.5, J14.5, R45.2, U3.3 (VI), U4.3 (VI)
/STM32F4/BOOT1: R49.2, U5.37 (PB2)
A1V2: B6.2, B7.2, U1.54 (VCC12A_PLL)
DAC1: J10.2, U5.29 (PA4)
EEP_DONE: D1.2 (A), R40.2, U1.21 (EEP_DONE)
ENC1_A: J11.4, R50.1, U5.23 (PA0)
ENC1_B: J11.3, R54.1, U5.24 (PA1)
ENC1_Z: J11.2, R58.1, U5.25 (PA2)
ENC2_A: J12.4, R51.1, U5.90 (PB4)
ENC2_B: J12.3, R55.1, U5.91 (PB5)
ENC2_Z: J12.2, R59.1, U5.92 (PB6)
ENC3_A: J13.4, R52.1, U5.59 (PD12)
ENC3_B: J13.3, R56.1, U5.60 (PD13)
ENC3_Z: J13.2, R60.1, U5.58 (PD11)
ENC4_A: J14.4, R53.1, U5.63 (PC6)
ENC4_B: J14.3, R57.1, U5.64 (PC7)
ENC4_Z: J14.2, R61.1, U5.67 (PA8)
GND: C1.2, C2.2, C3.2, C4.2, C5.2, C6.2, C7.2, C8.2, C9.2, C10.2, C11.2, C12.2, C13.2, C14.2, C15.2, C16.2, C17.2, C18.1, C19.1, C20.1, C21.1, C22.1, C23.1, C24.1, C25.1, C26.1, C27.1, C28.1, C29.2, C30.2, C31.2, C32.2, C33.2, C34.2, C35.2, C36.2, C37.2, C38.2, C39.2, C40.2, C41.2, C43.2, C44.2, C45.2, C46.2, C49.1, C51.1, C52.1, C53.1, D3.1 (K), D4.1 (K), D5.1 (K), IN1.8 (CHS_GND), IN1.10, IN1.SH (CHS_GND), J1.1, J2.2, J3.6, J4.6, J5.6, J6.2, J7.4, J8.4, J9.4, J10.3, J11.1, J12.1, J13.1, J14.1, OUT1.8 (CHS_GND), OUT1.10, OUT1.SH (CHS_GND), R2.2, R5.2, R6.2, R7.2, R11.2, R12.1, R27.2, R28.2, R30.1, R38.1, R39.1, R40.1, R48.1, R49.1, SW1.1, U1.56 (FM), U1.81 (GND_EPAD), U2.1 (A0), U2.2 (A1), U2.3 (A2), U2.4 (GND), U3.1 (GND), U4.1 (GND), U5.10 (VSS), U5.20 (VSSA), U5.27 (VSS), U5.74 (VSS), U5.99 (VSS), Y1.2, Y1.4
I2C2_SCL: J9.2, U5.47 (PB10)
I2C2_SDA: J9.3, U5.48 (PB11)
I2C_SCL: R1.1, R13.2, U2.6 (SCL)
I2C_SDA: R10.2, U1.63 (I2C_SDA), U2.5 (SDA)
IO1: J3.2, U5.34 (PC5)
IO2: J3.3, U5.35 (PB0)
IO3: J3.4, U5.36 (PB1)
IO4: J3.5, U5.38 (PE7)
IO5: J4.2, U5.39 (PE8)
IO6: J4.3, U5.40 (PE9)
IO7: J4.4, U5.41 (PE10)
IO8: J4.5, U5.42 (PE11)
IO9: J5.2, U5.43 (PE12)
IO10: J5.3, U5.44 (PE13)
IO11: J5.4, U5.45 (PE14)
IO12: J5.5, U5.46 (PE15)
LED_ERR: R38.2, R44.1, U1.20 (LED_ERR)
LED_RUN: D2.1 (K), R33.2, U1.19 (LED_RUN)
unnamed: D1.1 (K), R39.2
unnamed: D2.2 (A), R41.2
unnamed: D3.2 (A), R44.2
unnamed: D4.2 (A), R45.1
unnamed: D5.2 (A), R46.1
unnamed: IN1.9, R25.2
unnamed: B1.2, C27.2, IN1.4 (TCT), IN1.5 (RCT)
unnamed: OUT1.9, R26.2
unnamed: B2.2, C28.2, OUT1.4 (TCT), OUT1.5 (RCT)
unnamed: R1.2, U1.62 (I2C_SCL)
unnamed: R5.1, U1.34 (P0_SD)
unnamed: R7.1, U1.27 (P1_SD)
unnamed: R6.1, U1.33 (RESET_BG)
unnamed: R3.2, U1.6 (SPI_MISO)
unnamed: R2.1, U1.59 (TEST)
unnamed: R11.1, U2.7 (WP)
unnamed: R48.2, U5.94 (BOOT0)
unnamed: C51.2, U5.12 (PH0), Y2.2
unnamed: C52.2, U5.13 (PH1), Y2.1
unnamed: C49.2, U5.49 (VCAP_1)
unnamed: C53.2, U5.73 (VCAP_2)
P0_ACT: R25.1, R27.1, U1.40 (P0_ACT)
P0_RXIN: C25.2, IN1.6 (RD-), R23.1, U1.35 (P0_RXIN)
P0_RXIP: C23.2, IN1.3 (RD+), R21.1, U1.36 (P0_RXIP)
P0_TXON: C21.2, IN1.2 (TD-), R19.1, U1.37 (P0_TXON)
P0_TXOP: C19.2, IN1.1 (TD+), R17.1, U1.38 (P0_TXOP)
P1_ACT: R26.1, R28.1, U1.41 (P1_ACT)
P1_RXIN: C26.2, OUT1.6 (RD-), R24.1, U1.26 (P1_RXIN)
P1_RXIP: C24.2, OUT1.3 (RD+), R22.1, U1.25 (P1_RXIP)
P1_TXON: C22.2, OUT1.2 (TD-), R20.1, U1.24 (P1_TXON)
P1_TXOP: C20.2, OUT1.1 (TD+), R18.1, U1.23 (P1_TXOP)
PDI_EMU: R30.2, U1.61 (PDI_EMU)
RESET_MCU: C16.1, R8.1, SW1.2, U1.57 (RSTn)
RSTO: R12.2, U1.58 (RSTO)
RX: J6.3, U5.69 (PA10)
SCS_FUNC: U1.80 (SCS_FUNC), U5.9 (PC15)
SINT: U1.1 (SPI_INT), U5.15 (PC0)
SPI_CS: U1.79 (SCS_ESC), U5.33 (PC4)
SPI_MISO: R3.1, U5.31 (PA6)
SPI_MOSI: U1.78 (SPI_MOSI), U5.32 (PA7)
SPI_SCK: U1.64 (SPI_CLK), U5.30 (PA5)
STEP1_DIR: J7.2, U5.71 (PA12)
STEP1_STEP: J7.3, U5.70 (PA11)
STEP2_DIR: J8.2, U5.78 (PC10)
STEP2_STEP: J8.3, U5.66 (PC9)
SWCLK: J2.3, U5.76 (PA14)
SWDIO: J2.4, U5.72 (PA13)
SYNC0: U1.2 (SYNC_L0), U5.18 (PC3)
SYNC1: U1.3 (SYNC_L1), U5.16 (PC1)
TX: J6.4, U5.68 (PA9)
XSCI: C15.1, U1.31 (XSCI), Y1.1
XSCO: C17.1, U1.30 (XSCO), Y1.3
